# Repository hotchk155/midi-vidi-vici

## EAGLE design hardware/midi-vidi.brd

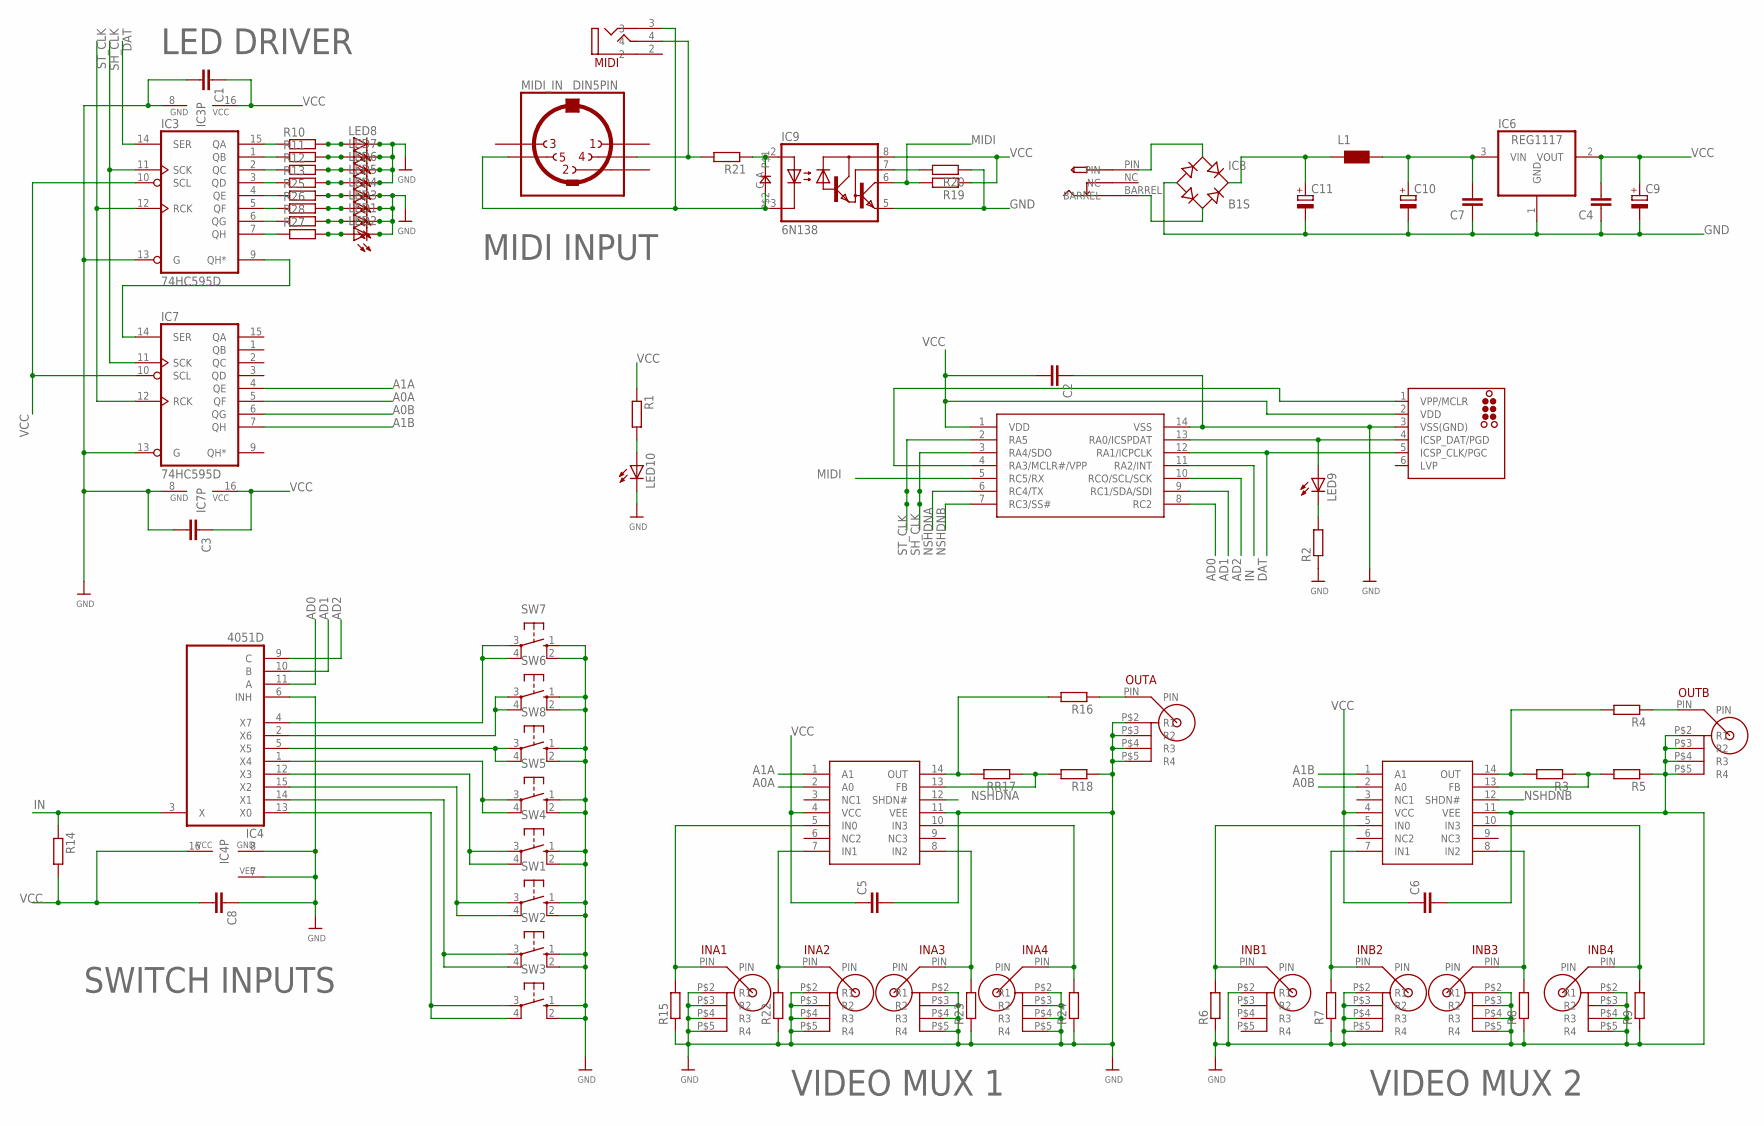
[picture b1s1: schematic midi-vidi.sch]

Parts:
C1, C2, C3, C4, C5, C6, C7, C8: C-EUC0805; C0805
C9, C10, C11: CPOL-EUE2,5-6E; E2,5-6E
D1: 0805DIODE
IC1, IC5: MAX4311SO14; SO14
IC2: PIC16F1825SO14; SO14
IC3, IC7: 74HC595D; SO16
IC4: 4051D; SO16
IC6: REG1117; SOT223
IC8: B1S; MBS
IC9: 6N138; DIL08
ICSP: TC2030-MCP-NL
INA1, INA2, INA3, INA4: RCAVERT
INB1, INB2, INB3, INB4: RCAVERT
L1: WE-TI_L
LED1, LED2, LED3, LED4, LED5, LED6, LED7, LED8, LED9, LED10: LED3MM
MIDI: VERTICAL_3_5MM_SOCKET
MIDI_IN: DIN5PIN; EDGEDIN
OUTA: RCAVERT
OUTB: RCAVERT
R1, R2, R3, R4, R5, R6, R7, R8, R9, R10, R11, R12, R13, R14, R15, R16, R18, R19, R20, R21, R22, R23, R24, R25, R26, R27, R28: R-EU_R0805; R0805
RR17: R-EU_R0805; R0805
SW1, SW2, SW3, SW4, SW5, SW6, SW7, SW8: 10-XX; B3F-10XX
U$2: PWR_SOCKET_2_1MM

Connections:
A0A: IC5.2 (A0), IC7.5 (QF)
A0B: IC1.2 (A0), IC7.6 (QG)
A1A: IC5.1 (A1), IC7.4 (QE)
A1B: IC1.1 (A1), IC7.7 (QH)
AD0: IC2.8 (RC2), IC4.11 (A)
AD1: IC2.9 (RC1/SDA/SDI), IC4.10 (B)
AD2: IC2.10 (RCO/SCL/SCK), IC4.9 (C)
DAT: IC2.12 (RA1/ICPCLK), IC3.14 (SER), ICSP.5 (ICSP_CLK/PGC)
GND: C1.2, C2.1, C3.2, C4.1, C5.2, C6.2, C7.1, C8.1, C9.-, C10.-, C11.-, IC1.11 (VEE), IC2.14 (VSS), IC3.8 (GND), IC3.13 (G), IC4.6 (INH), IC4.7 (VEE), IC4.8 (GND), IC5.11 (VEE), IC6.1 (GND), IC7.8 (GND), IC7.13 (G), IC8.-, IC9.5 (GND), ICSP.3 (VSS(GND)), INA1.P$2 (R1), INA1.P$3 (R2), INA1.P$4 (R3), INA1.P$5 (R4), INA2.P$2 (R1), INA2.P$3 (R2), INA2.P$4 (R3), INA2.P$5 (R4), INA3.P$2 (R1), INA3.P$3 (R2), INA3.P$4 (R3), INA3.P$5 (R4), INA4.P$2 (R1), INA4.P$3 (R2), INA4.P$4 (R3), INA4.P$5 (R4), INB1.P$2 (R1), INB2.P$2 (R1), INB2.P$3 (R2), INB2.P$4 (R3), INB2.P$5 (R4), INB3.P$2 (R1), INB3.P$3 (R2), INB3.P$4 (R3), INB3.P$5 (R4), INB4.P$2 (R1), INB4.P$3 (R2), INB4.P$4 (R3), INB4.P$5 (R4), LED1.K (C), LED2.K (C), LED3.K (C), LED4.K (C), LED5.K (C), LED6.K (C), LED7.K (C), LED8.K (C), LED10.K (C), OUTA.P$2 (R1), OUTA.P$3 (R2), OUTA.P$4 (R3), OUTA.P$5 (R4), OUTB.P$2 (R1), OUTB.P$3 (R2), OUTB.P$4 (R3), OUTB.P$5 (R4), R2.1, R5.1, R6.1, R7.1, R8.1, R9.1, R15.1, R18.1, R20.1, R22.1, R23.1, R24.1, SW1.1 (S), SW1.2 (S1), SW2.1 (S), SW2.2 (S1), SW3.1 (S), SW3.2 (S1), SW4.1 (S), SW4.2 (S1), SW5.1 (S), SW5.2 (S1), SW6.1 (S), SW6.2 (S1), SW7.1 (S), SW7.2 (S1), SW8.1 (S), SW8.2 (S1)
IN: IC2.11 (RA2/INT), IC4.3 (X), R14.1
MIDI: IC2.5 (RC5/RX), IC9.6 (VO), R19.2
unnamed: IC5.10 (IN3), INA4.PIN, R24.2
unnamed: IC5.8 (IN2), INA3.PIN, R23.2
unnamed: IC5.7 (IN1), INA2.PIN, R22.2
unnamed: IC5.5 (IN0), INA1.PIN, R15.2
unnamed: IC5.14 (OUT), R16.2, RR17.2
unnamed: IC5.13 (FB), R18.2, RR17.1
unnamed: OUTA.PIN, R16.1
unnamed: D1.A, IC9.2 (A), R21.1
unnamed: MIDI.4, MIDI_IN.4, R21.2
unnamed: IC1.7 (IN1), INB2.PIN, R7.2
unnamed: IC1.8 (IN2), INB3.PIN, R8.2
unnamed: IC1.5 (IN0), INB1.PIN, R6.2
unnamed: IC1.14 (OUT), R3.2, R4.2
unnamed: IC1.13 (FB), R3.1, R5.2
unnamed: C7.2, C10.+, IC6.3 (VIN), L1.1 (2)
unnamed: OUTB.PIN, R4.1
unnamed: IC1.10 (IN3), INB4.PIN, R9.2
unnamed: D1.C, IC9.3 (C), MIDI.3, MIDI_IN.5
unnamed: LED8.A, R10.2
unnamed: LED7.A, R11.2
unnamed: LED6.A, R12.2
unnamed: IC9.7 (VB), R20.2
unnamed: IC3.15 (QA), R10.1
unnamed: LED5.A, R13.2
unnamed: IC3.1 (QB), R11.1
unnamed: IC3.2 (QC), R12.1
unnamed: IC3.3 (QD), R13.1
unnamed: IC3.4 (QE), R25.1
unnamed: IC3.5 (QF), R26.1
unnamed: IC3.6 (QG), R28.1
unnamed: IC3.7 (QH), R27.1
unnamed: LED4.A, R25.2
unnamed: LED3.A, R26.2
unnamed: LED1.A, R28.2
unnamed: LED2.A, R27.2
unnamed: LED9.K (C), R2.2
unnamed: IC4.4 (X7), SW7.3, SW7.4 (P1)
unnamed: IC4.2 (X6), SW6.3, SW6.4 (P1)
unnamed: IC4.5 (X5), SW8.3, SW8.4 (P1)
unnamed: IC4.1 (X4), SW5.3, SW5.4 (P1)
unnamed: IC4.12 (X3), SW4.3, SW4.4 (P1)
unnamed: IC4.15 (X2), SW1.3, SW1.4 (P1)
unnamed: IC4.14 (X1), SW2.3, SW2.4 (P1)
unnamed: IC4.13 (X0), SW3.3, SW3.4 (P1)
unnamed: IC2.13 (RA0/ICSPDAT), ICSP.4 (ICSP_DAT/PGD), LED9.A
unnamed: IC8.AC1, U$2.PIN
unnamed: IC3.9 (QH*), IC7.14 (SER)
unnamed: IC2.4 (RA3/MCLR#/VPP), ICSP.1 (VPP/MCLR)
unnamed: IC8.AC2, U$2.BARREL
unnamed: LED10.A, R1.2
unnamed: C11.+, IC8.+, L1.2 (1)
NSHDNA: IC2.6 (RC4/TX), IC5.12 (SHDN#)
NSHDNB: IC1.12 (SHDN#), IC2.7 (RC3/SS#)
SH_CLK: IC2.3 (RA4/SDO), IC3.11 (SCK), IC7.11 (SCK)
ST_CLK: IC2.2 (RA5), IC3.12 (RCK), IC7.12 (RCK)
VCC: C1.1, C2.2, C3.1, C4.2, C5.1, C6.1, C8.2, C9.+, IC1.4 (VCC), IC2.1 (VDD), IC3.10 (SCL), IC3.16 (VCC), IC4.16 (VCC), IC5.4 (VCC), IC6.2 (VOUT), IC7.10 (SCL), IC7.16 (VCC), IC9.8 (VCC), ICSP.2 (VDD), R1.1, R14.2, R19.1

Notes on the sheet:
VIDEO MUX 1
VIDEO MUX 2
SWITCH INPUTS
LED DRIVER
MIDI INPUT

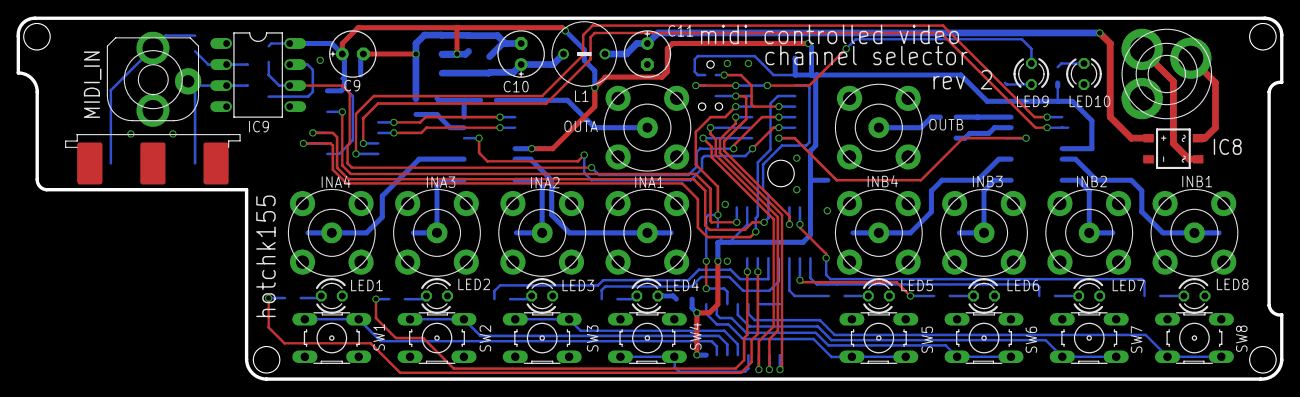
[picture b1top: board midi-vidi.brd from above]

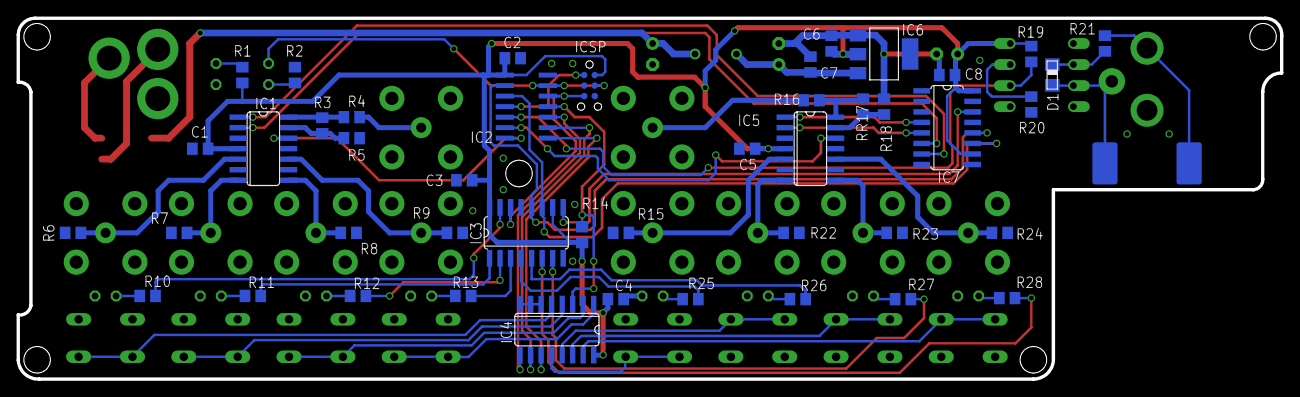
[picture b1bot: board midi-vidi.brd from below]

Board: 2 copper layers, 152.5 x 43.6 mm, 82 parts (45 on the bottom side), 67 nets.

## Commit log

2016-05-29 :boom::camel: Added .gitattributes & .gitignore files
2016-05-29 ideas
2016-06-11 ready?
2016-06-13 PCB rev 1
2016-06-14 Fix DRC issues - FINAL REV 1 PCB
2016-07-18 updates - working for rev2

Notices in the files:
parts and their libraries:
tag-connect: ©2009 ROFA.cz - modified and updated by Robert Darlington ‹rdarlington@gmail.com›
wuerth-elektronik: Copyright: Würth Elektronik eiSos
